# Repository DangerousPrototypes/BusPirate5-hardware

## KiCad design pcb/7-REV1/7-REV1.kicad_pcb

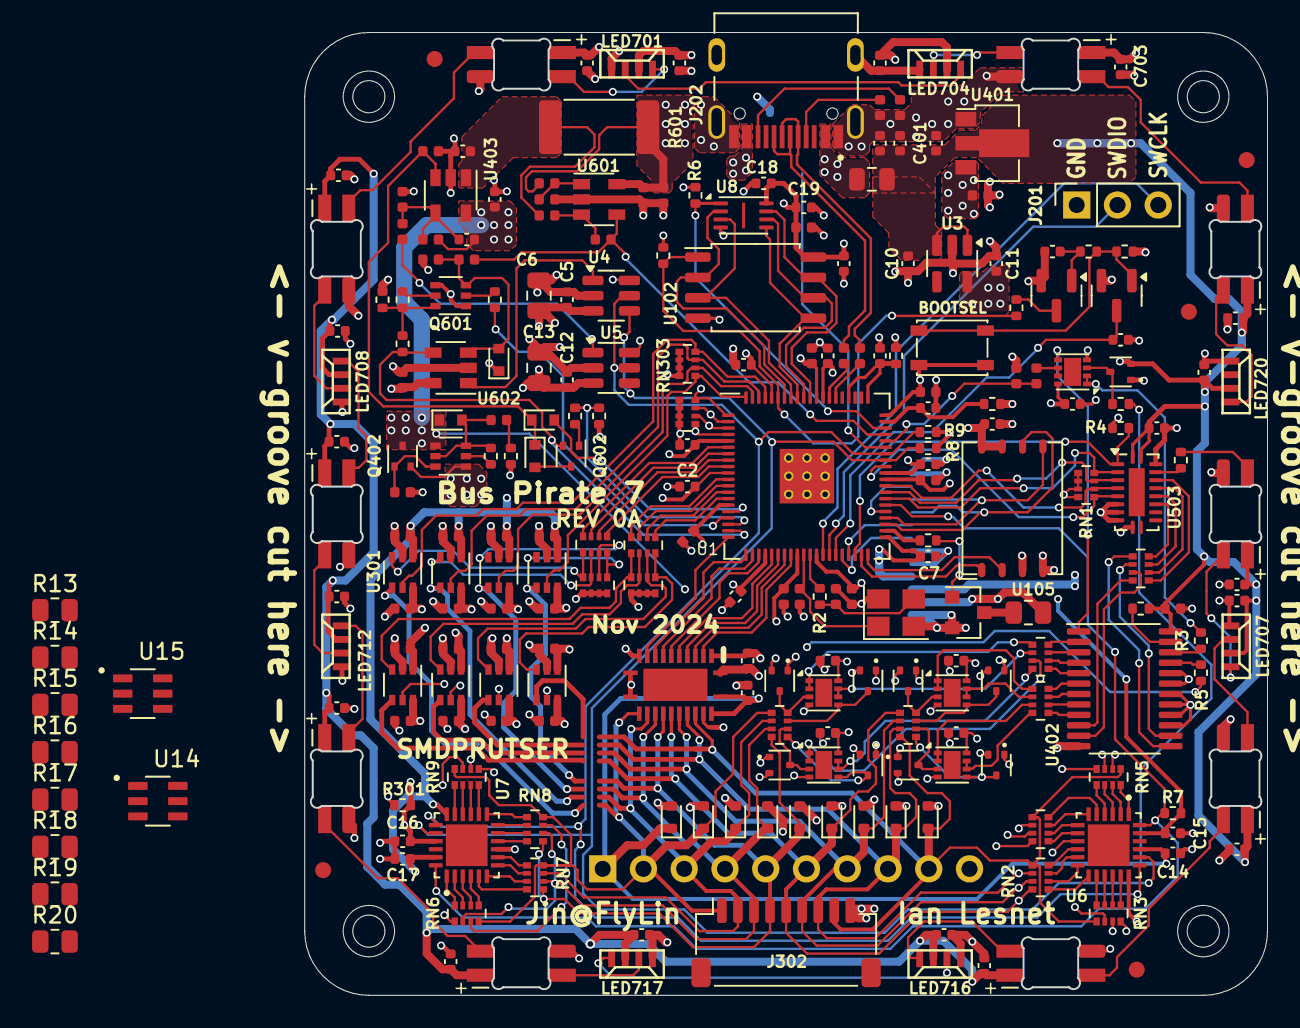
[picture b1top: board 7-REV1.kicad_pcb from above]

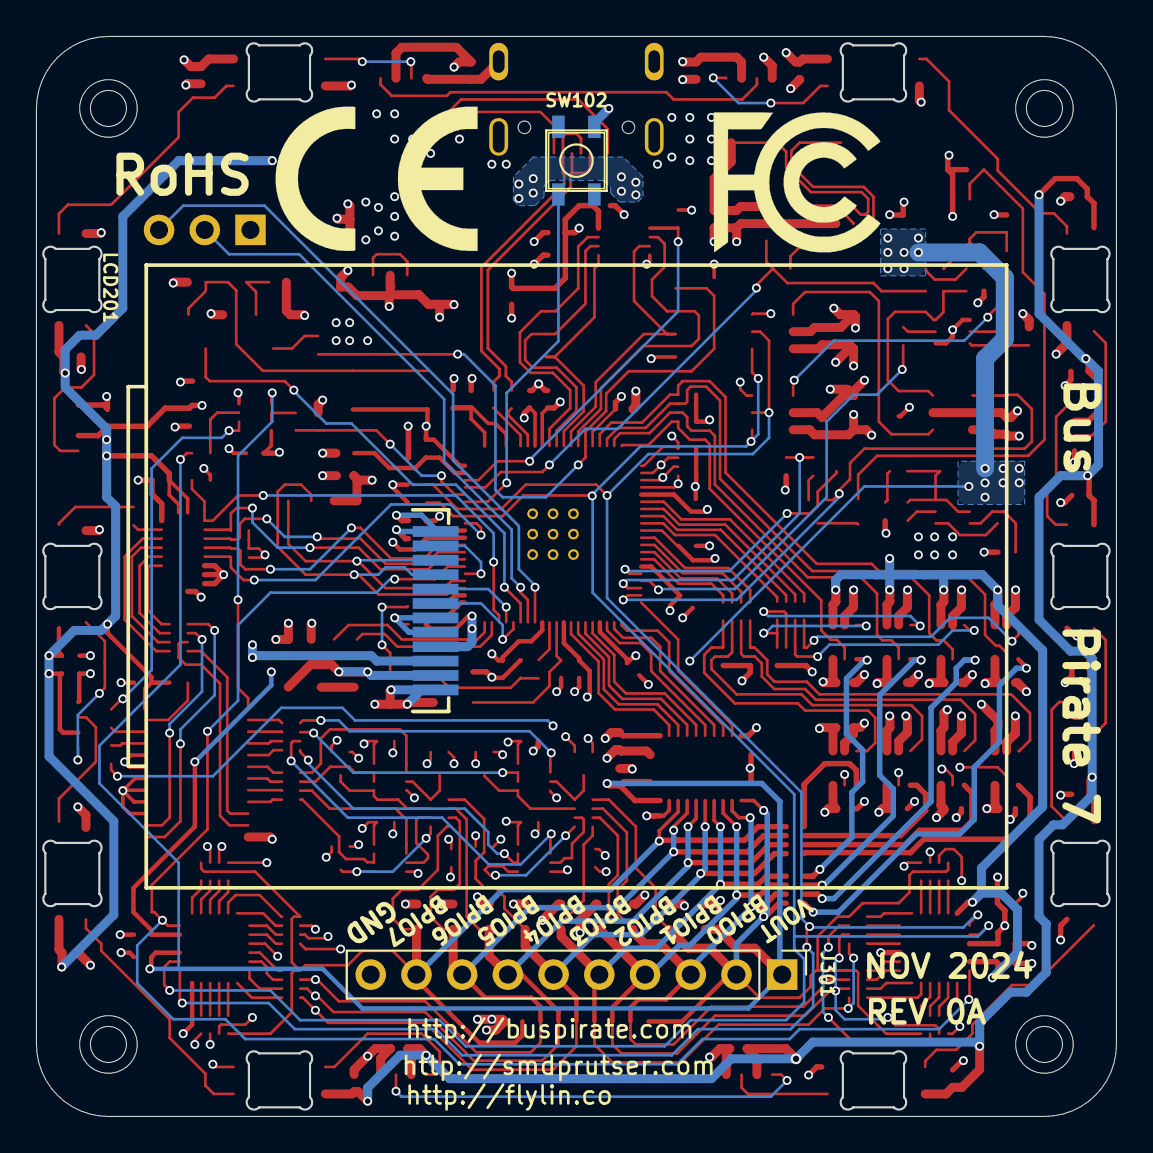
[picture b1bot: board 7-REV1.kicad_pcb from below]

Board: 4 copper layers, 60.0 x 60.0 mm, 260 parts (5 on the bottom side), 212 nets.

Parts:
C1, C2, C3, C5, C7, C8, C9, C12, C14, C15, C16, C17, C18, C20, C22, C103, C110, C111, C112, C113, C114, C115, C116, C117, C118, C121, C301, C302, C303, C304, C305, C306, C307, C308, C309, C310, C311, C312, C313, C314, C315, C316, C403, C503, C507, C508, C509, C510, C602, C605, C701, C702, C703, C704, C705, C706, C707, C708, C710, C712, C713, C714, C715, C716, C717, C718, C719, C720: 0.1uF; C_0402_1005Metric
C4, C19, C104, C109, C601: 2.2uF; C_0402_1005Metric
C6, C13: 10uF; C_0805_2012Metric
C10, C11, C201, C202, C401, C402, C404, C407: 4.7uF; C_0402_1005Metric
C21: 10uF; C_0402_1005Metric
C105, C106: 15pF; C_0402_1005Metric
C408: 120pF; C_0402_1005Metric
C603: DNF; C_0402_1005Metric
D1, D2, D3, D4, D5, D6, D7, D8, D9: BAS40-04; SOT-523
D10, D11, D12, D13, D14, D15, D16, D17, D18: DESD5Z5.0; D_SOD-523
D401, D601, D602, D603: 1N4148WT; D_SOD-523
FID1, FID2, FID3, FID4, FID5: Fiducial; Fiducial_1mm_Mask2mm
H1, H2, H3, H4: MountingHole; MountingHole_3.2mm_M3
J201: Conn_01x03; PinSocket_1x03_P2.54mm_Vertical
J202: TYPE-C-31-M-12; HRO_TYPE-C-31-M-12
J301: Conn_01x10; PinHeader_1x10_P2.54mm_Vertical
J302: Conn_01x09; JST_SH_SM09B-SRSS-TB_1x09-1MP_P1.00mm_Horizontal
L201: CBW201209U300T; L_0805_2012Metric
LCD201: TFT_20_QT200H1201
LED701, LED704, LED707, LED708, LED712, LED716, LED717, LED720: SK6812-side-a_b
LED702, LED703, LED705, LED706, LED710, LED713, LED714, LED715, LED718, LED719: SK6812-mini-e; SK6812-MINI-E
Q1, Q2, Q202: MMBT7002K; SOT-23
Q401: BCM857; SOT-363_SC-70-6
Q402, Q602: BC2301T 2.8A; SOT-523
Q601: MMDT3906; SOT-363_SC-70-6
R1: 10R; R_0402_1005Metric
R2, R12, R502, R602, R603: 1K; R_0402_1005Metric
R3, R5, R320: 510R; R_0402_1005Metric
R4, R6, R7, R319, R401, R412: 100K; R_0402_1005Metric
R8, R9, R11, R301, R406, R407, R410, R606, R609, R610, R611, R613: 10K; R_0402_1005Metric
R10: 470K; R_0402_1005Metric
R13, R14, R15, R16, R17, R18, R19, R20: 120R; R_0805_2012Metric
R102: DNF; R_0402_1005Metric
R103, R208, R608, R612: 200R; R_0402_1005Metric
R201, R204: 5.1K; R_0402_1005Metric
R202, R203: 22R; R_0402_1005Metric
R209: 33R; R_0805_2012Metric
R403: 102K; R_0402_1005Metric
R404: 133K; R_0402_1005Metric
R405, R408, R409, R604, R605: 33K; R_0402_1005Metric
R601: 0R2; R_2512_6332Metric_Pad1.40x3.35mm_HandSolder
RN1, RN302, RN303, RN307, RN308, RN317, RN318: 100K; R_Array_Convex_4x0402
RN2, RN8: 1M; R_Array_Convex_4x0402
RN3, RN9: 10K; R_Array_Convex_4x0402
RN4, RN7: 4.7K; R_Array_Convex_4x0402
RN5, RN6: 2.2K; R_Array_Convex_4x0402
RN301, RN306: 330R; R_Array_Convex_4x0402
RN315, RN400, RN401: 510R; R_Array_Convex_4x0402
SW101: TS3425BA 098 2.5H 250gf; SW_SPST_PTS810
SW102: TS3315A 250gf 025; GT-TC026X-HXXX-LX
U1: RP2350B; qfn80
U2: 74LVC8T245BQ; NXP-DHVQFN24
U3: TLV74311PDBVR; SOT-23-5
U4, U5: MCP4725xxx-xCH; SOT-23-6
U6, U7: TCA6416RTWT; QFN50P400X400X80-25N
U8: APS6404L-3SQR-ZR; Winbond_USON-8-1EP_3x2mm_P0.5mm_EP0.2x1.6mm
U9, U10, U11, U12, U13: LM358_DFN; DFN-8-1EP_2x2mm_P0.5mm_EP1.05x1.75mm
U14, U15: IP4220CZ6F; SOT95P275X110-6N
U102: W25Q128JVSIQ; SOP-8_5.28x5.23mm_P1.27mm
U105: MT29F1G01ABAFDWB; U-PDFN-8
U301, U302, U303, U304, U305, U306, U307, U308: AiP74LVC1T45GC363.TR; SOT-363_SC-70-6
U401: ME6211A33PG-N; SOT-89-3
U402: CD4067; TSSOP-24_4.4x7.8mm_P0.65mm
U403: AP2127; SOT-23-5
U503: 74HCT245BQ; DHVQFN-20-1EP_2.5x4.5mm_P0.5mm_EP1x3mm
U601: GS321A-TR; SOT-23-5
U602: GSV331-TR; SOT-23-5
Y101: ABM8-272-T3; Crystal_SMD_3225-4Pin_3.2x2.5mm
logo1: fcc_logo; logo_fcc
logo2: ce_logo; CE-Logo_11.2x8mm_SilkScreen

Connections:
+1V1: C2.1, C11.1, C117.1, C118.1, U1.10 (DVDD), U1.32 (DVDD), U1.51 (DVDD), U3.5 (VOUT)
+3V3: C1.1, C3.2, C5.1, C6.1, C7.1, C8.1, C12.1, C13.1, C15.2, C17.2, C18.1, C19.1, C103.1, C104.1, C110.1, C111.1, C112.1, C113.1, C114.1, C115.1, C116.1, C121.1, C301.2, C302.2, C303.2, C307.2, C308.2, C309.2, C313.2, C314.2, C402.1, C605.1, D601.1 (K), LCD201.4 (VCC), Q601.1 (E1), Q601.4 (E2), R1.1, R6.1, R7.1, R8.1, R9.1, R102.1, R103.1, R609.1, R613.1, SW101.1 (A), U1.5 (IOVDD), U1.15 (IOVDD), U1.24 (IOVDD), U1.29 (IOVDD), U1.41 (IOVDD), U1.50 (IOVDD), U1.60 (IOVDD), U1.68 (USB_OTP_VDD), U1.69 (QSPI_IOVDD), U1.76 (IOVDD), U2.1 (VCCA), U4.3 (VDD), U5.3 (VDD), U5.6 (A0), U6.23 (VCCI), U7.18 (ADDR), U7.23 (VCCI), U8.8 (VCC), U102.8 (VCC), U105.3 (WP/IO2), U105.7 (HOLD/IO3), U105.8 (VCC), U301.1 (VCCA), U302.1 (VCCA), U303.1 (VCCA), U304.1 (VCCA), U305.1 (VCCA), U306.1 (VCCA), U307.1 (VCCA), U308.1 (VCCA), U401.3 (VOUT), U602.5 (V+)
+VUSB: C10.1, C20.2, C201.2, C202.2, C401.1, C403.2, C503.2, C507.2, C508.2, C509.2, C510.2, C601.1, C602.2, C701.2, C702.2, C703.2, C704.2, C705.2, C706.2, C707.2, C708.2, C710.2, C712.2, C713.2, C714.2, C715.2, C716.2, C717.2, C718.2, C719.2, C720.2, D1.2, D2.2, D3.2, D4.2, D5.2, D6.2, D7.2, D8.2, D9.2, L201.1, LCD201.3 (LED-A), LED701.3 (VDD), LED702.1 (VDD), LED703.1 (VDD), LED704.3 (VDD), LED705.1 (VDD), LED706.1 (VDD), LED707.3 (VDD), LED708.3 (VDD), LED710.1 (VDD), LED712.3 (VDD), LED713.1 (VDD), LED714.1 (VDD), LED715.1 (VDD), LED716.3 (VDD), LED717.3 (VDD), LED718.1 (VDD), LED719.1 (VDD), LED720.3 (VDD), R320.2, R601.1, R602.2, U3.1 (VIN), U3.3 (~SHDN), U9.8 (V+), U10.8 (V+), U11.8 (V+), U12.8 (V+), U13.8 (V+), U14.5 (VP), U15.5 (VP), U401.2 (VIN), U402.24 (VCC), U503.1 (A->B), U503.20 (VCC), U601.5 (V+)
AMUX_OUT: R406.2, R407.2, U1.56 (GPIO45_ADC5)
AMUX_S0: RN315.4 (R1.1), U402.10 (S0)
AMUX_S0_3V3: RN1.8 (R1.8), U1.47 (GPIO38), U503.3 (A1)
AMUX_S1: RN315.3 (R1.1), U402.11 (S1)
AMUX_S1_3V3: RN1.7 (R1.8), U1.48 (GPIO39), U503.4 (A2)
AMUX_S2: RN315.2 (R1.1), U402.14 (S2)
AMUX_S2_3V3: RN1.6 (R1.8), U1.49 (GPIO40_ADC0), U503.5 (A3)
AMUX_S3: RN315.1 (R1.1), U402.13 (S3)
AMUX_S3_3V3: RN1.5 (R1.8), U1.52 (GPIO41_ADC1), U503.6 (A4)
BPIO0: D10.1 (K), R13.1, RN6.4 (R1.1), RN7.4 (R1.1), RN8.8 (R1.8), RN9.8 (R1.8), RN318.5 (R1.8), U2.14 (B8), U14.1 (I/O_1), U301.4 (B)
BPIO1: D11.1 (K), R14.1, RN6.3 (R1.1), RN7.3 (R1.1), RN8.7 (R1.8), RN9.7 (R1.8), RN318.6 (R1.8), U2.15 (B7), U14.3 (I/O_2), U302.4 (B)
BPIO2: D13.1 (K), R15.1, RN6.2 (R1.1), RN7.2 (R1.1), RN8.6 (R1.8), RN9.6 (R1.8), RN318.7 (R1.8), U2.16 (B6), U14.4 (I/O_3), U303.4 (B)
BPIO3: D12.1 (K), R16.1, RN6.1 (R1.1), RN7.1 (R1.1), RN8.5 (R1.8), RN9.5 (R1.8), RN318.8 (R1.8), U2.17 (B5), U14.6 (I/O_4), U304.4 (B)
BPIO4: D17.1 (K), R17.1, RN2.8 (R1.8), RN3.8 (R1.8), RN4.4 (R1.1), RN5.4 (R1.1), RN317.5 (R1.8), U2.18 (B4), U15.1 (I/O_1), U305.4 (B)
BPIO5: D16.1 (K), R18.1, RN2.7 (R1.8), RN3.7 (R1.8), RN4.3 (R1.1), RN5.3 (R1.1), RN317.6 (R1.8), U2.19 (B3), U15.3 (I/O_2), U306.4 (B)
BPIO6: D15.1 (K), R19.1, RN2.6 (R1.8), RN3.6 (R1.8), RN4.2 (R1.1), RN5.2 (R1.1), RN317.7 (R1.8), U2.20 (B2), U15.4 (I/O_3), U307.4 (B)
BPIO7: D14.1 (K), R20.1, RN2.5 (R1.8), RN3.5 (R1.8), RN4.1 (R1.1), RN5.1 (R1.1), RN317.8 (R1.8), U2.21 (B1), U15.6 (I/O_4), U308.4 (B)
BUFDIR0: RN303.8 (R1.8), U1.77 (GPIO0), U301.5 (DIR)
BUFDIR1: RN303.7 (R1.8), U1.78 (GPIO1), U302.5 (DIR)
BUFDIR2: RN303.6 (R1.8), U1.79 (GPIO2), U303.5 (DIR)
BUFDIR3: RN303.5 (R1.8), U1.80 (GPIO3), U304.5 (DIR)
BUFDIR4: RN308.8 (R1.8), U1.1 (GPIO4), U305.5 (DIR)
BUFDIR5: RN308.7 (R1.8), U1.2 (GPIO5), U306.5 (DIR)
BUFDIR6: RN308.6 (R1.8), U1.3 (GPIO6), U307.5 (DIR)
BUFDIR7: RN308.5 (R1.8), U1.4 (GPIO7), U308.5 (DIR)
BUFIO0: RN301.8 (R1.8), U1.6 (GPIO8)
BUFIO1: RN301.7 (R1.8), U1.7 (GPIO9)
BUFIO2: RN301.6 (R1.8), U1.8 (GPIO10)
BUFIO3: RN301.5 (R1.8), U1.9 (GPIO11)
BUFIO4: RN306.8 (R1.8), U1.11 (GPIO12)
BUFIO5: RN306.7 (R1.8), U1.12 (GPIO13)
BUFIO6: RN306.6 (R1.8), U1.13 (GPIO14)
BUFIO7: RN306.5 (R1.8), U1.14 (GPIO15)
BUTTONS: SW102.1, U1.55 (GPIO44_ADC4)
CURRENT_ADJ_MCU: U4.1 (VOUT), U602.1 (+)
CURRENT_DETECT: Q602.2 (S), R610.2, U1.19 (GPIO19), U602.4
CURRENT_EN: R612.2, R613.2, U1.18 (GPIO18)
CURRENT_EN_OVERRIDE: D603.2 (A), U1.16 (GPIO16)
CURRENT_RESET: R611.1, U1.17 (GPIO17)
CURRENT_SENSE: R605.1, R606.2, U1.57 (GPIO46_ADC6), U601.4
DISPLAY_BACKLIGHT: R208.1, U1.42 (GPIO33)
DISPLAY_CS: LCD201.8 (CS), U1.37 (GPIO29)
DISPLAY_DP: LCD201.7 (WR/SPI_A0), U1.36 (GPIO28)
DISPLAY_LED-K: LCD201.2 (LED-K), R209.2
DISPLAY_RESET: LCD201.11 (RESET), U1.45 (GPIO36)
FLASH_CS: U1.39 (GPIO31), U105.1 (CS)
GND: C1.2, C2.2, C3.1, C4.2, C5.2, C6.2, C7.2, C8.2, C9.2, C10.2, C11.2, C12.2, C13.2, C14.1, C15.1, C16.1, C17.1, C18.2, C19.2, C20.1, C21.2, C22.2, C103.2, C104.2, C105.2, C106.2, C109.2, C110.2, C111.2, C112.2, C113.2, C114.2, C115.2, C116.2, C117.2, C118.2, C121.2, C201.1, C202.1, C301.1, C302.1, C303.1, C304.2, C305.2, C306.2, C307.1, C308.1, C309.1, C310.2, C311.2, C312.2, C313.1, C314.1, C315.2, C316.2, C401.2, C402.2, C403.1, C404.2, C407.2, C503.1, C507.1, C508.1, C509.1, C510.1, C601.2, C602.1, C603.1, C605.2, C701.1, C702.1, C703.1, C704.1, C705.1, C706.1, C707.1, C708.1, C710.1, C712.1, C713.1, C714.1, C715.1, C716.1, C717.1, C718.1, C719.1, C720.1, D1.1, D2.1, D3.1, D4.1, D5.1, D6.1, D7.1, D8.1, D9.1, D10.2 (A), D11.2 (A), D12.2 (A), D13.2 (A), D14.2 (A), D15.2 (A), D16.2 (A), D17.2 (A), D18.2 (A), J201.1, J202.A1B12 (GND), J202.B1A12 (GND), J202.S1 (SHIELD), J202.S2 (SHIELD), J202.S3 (SHIELD), J202.S4 (SHIELD), J301.10, J302.9, LCD201.1 (GND), LCD201.5 (GND), LCD201.6 (GND), LCD201.12 (GND), LED701.1 (VSS), LED702.3 (VSS), LED703.3 (VSS), LED704.1 (VSS), LED705.3 (VSS), LED706.3 (VSS), LED707.1 (VSS), LED708.1 (VSS), LED710.3 (VSS), LED712.1 (VSS), LED713.3 (VSS), LED714.3 (VSS), LED715.3 (VSS), LED716.1 (VSS), LED717.1 (VSS), LED718.3 (VSS), LED719.3 (VSS), LED720.1 (VSS), Q1.2 (S), Q2.2 (S), Q202.2 (S), R4.1, R11.2, R201.1, R204.1, R301.2, R401.2, R405.2, R407.1, R409.2, R412.2, R604.1, RN1.1 (R1.1), RN1.2 (R1.1), RN1.3 (R1.1), RN1.4 (R1.1), RN302.1 (R1.1), RN302.2 (R1.1), RN302.3 (R1.1), RN302.4 (R1.1), RN303.1 (R1.1), RN303.2 (R1.1), RN303.3 (R1.1), RN303.4 (R1.1), RN307.1 (R1.1), RN307.2 (R1.1), RN307.3 (R1.1), RN307.4 (R1.1), RN308.1 (R1.1), RN308.2 (R1.1), RN308.3 (R1.1), RN308.4 (R1.1), SW102.4, U1.81 (GND), U2.2 (DIR), U2.11 (GND), U2.12 (GND), U2.13 (GND), U2.22 (~OE), U3.2 (GND), U4.2 (VSS), U4.6 (A0), U5.2 (VSS), U6.9 (GND), U6.18 (ADDR), U7.9 (GND), U8.4 (VSS), U9.4 (V-), U10.4 (V-), U11.4 (V-), U12.4 (V-), U13.4 (V-), U14.2 (GND), U15.2 (GND), U102.4 (VSS), U105.4 (VSS), U301.2 (GND), U302.2 (GND), U303.2 (GND), U304.2 (GND), U305.2 (GND), U306.2 (GND), U307.2 (GND), U308.2 (GND), U401.1 (GND), U402.12 (GND), U402.15 (~E), U402.16 (I15), U402.17 (I14), U402.18 (I13), U402.19 (I12), U402.20 (I11), U403.2 (GND), U503.7 (A5), U503.8 (A6), U503.9 (A7), U503.10 (GND), U503.19 (CE), U601.2 (V-), U602.2 (V-), Y101.2, Y101.4
I2C_RESET: R7.2, U1.46 (GPIO37), U6.24 (~RESET), U7.24 (~RESET)
I2C_SCL: R9.2, U1.54 (GPIO43_ADC3), U4.5 (SCL), U5.5 (SCL), U6.19 (SCL), U7.19 (SCL)
I2C_SDA: R8.2, U1.53 (GPIO42_ADC2), U4.4 (SDA), U5.4 (SDA), U6.20 (SDA), U7.20 (SDA)
LA_BPIO0: U1.20 (GPIO20), U2.10 (A8)
LA_BPIO1: U1.21 (GPIO21), U2.9 (A7)
LA_BPIO2: U1.22 (GPIO22), U2.8 (A6)
LA_BPIO3: U1.23 (GPIO23), U2.7 (A5)
LA_BPIO4: U1.25 (GPIO24), U2.6 (A4)
LA_BPIO5: U1.26 (GPIO25), U2.5 (A3)
LA_BPIO6: U1.27 (GPIO26), U2.4 (A2)
LA_BPIO7: U1.28 (GPIO27), U2.3 (A1)
LEDS_CDO: R502.1, U503.18 (B0)
MCU_BOOTLOAD: R12.2, R102.2, U1.75 (QSPI_SS), U102.1 (CS)
MCU_RESET: C22.1, Q1.3 (D), U1.35 (RUN)
MUX_BPIO0: RN401.5 (R1.8), U9.1, U9.2 (-)
MUX_BPIO1: RN401.6 (R1.8), U9.6 (-), U9.7
MUX_BPIO2: RN401.7 (R1.8), U10.1, U10.2 (-)
MUX_BPIO3: RN401.8 (R1.8), U10.6 (-), U10.7
MUX_BPIO4: RN400.5 (R1.8), U11.1, U11.2 (-)
MUX_BPIO5: RN400.6 (R1.8), U11.6 (-), U11.7
MUX_BPIO6: RN400.7 (R1.8), U12.1, U12.2 (-)
MUX_BPIO7: RN400.8 (R1.8), U12.6 (-), U12.7
MUX_VREF_VOUT: R3.2, U13.1, U13.2 (-)
unnamed: C106.1, R2.1, Y101.3
unnamed: D401.2 (A), Q401.3 (C2), Q401.5 (B2), R408.2, R410.2
unnamed: C603.2, D601.2 (A), Q601.3 (C2), R606.1, U602.3 (-)
unnamed: D602.2 (A), Q602.3 (D)
unnamed: J202.A5 (CC1), R201.2
unnamed: J202.B5 (CC2), R204.2
unnamed: J202.A4B9 (VBUS), J202.B4A9 (VBUS), L201.2
unnamed: J301.2, J302.1, R13.2
unnamed: J301.3, J302.2, R14.2
unnamed: J301.4, J302.3, R15.2
unnamed: J301.5, J302.4, R16.2
unnamed: J301.6, J302.5, R17.2
unnamed: J301.7, J302.6, R18.2
unnamed: J301.8, J302.7, R19.2
unnamed: J301.9, J302.8, R20.2
unnamed: LED701.4 (DI), LED702.2 (DO)
unnamed: LED701.2 (DO), LED704.4 (DI)
unnamed: LED702.4 (DI), LED706.2 (DO)
unnamed: LED703.4 (DI), LED704.2 (DO)
unnamed: LED703.2 (DO), LED705.4 (DI)
unnamed: LED705.2 (DO), LED720.4 (DI)
unnamed: LED706.4 (DI), LED708.2 (DO)
unnamed: LED707.4 (DI), LED719.2 (DO)
unnamed: LED707.2 (DO), LED713.4 (DI)
unnamed: LED708.4 (DI), LED710.2 (DO)
unnamed: LED710.4 (DI), LED712.2 (DO)
unnamed: LED712.4 (DI), LED714.2 (DO)
unnamed: LED713.2 (DO), LED715.4 (DI)
unnamed: LED714.4 (DI), LED718.2 (DO)
unnamed: LED715.2 (DO), LED716.4 (DI)
unnamed: LED716.2 (DO), LED717.4 (DI)
unnamed: LED717.2 (DO), LED718.4 (DI)
unnamed: LED719.4 (DI), R502.2
unnamed: Q1.1 (G), R10.1, R11.1, SW101.2 (B)
unnamed: Q2.3 (D), R12.1
unnamed: C21.1, Q2.1 (G), R10.2
unnamed: Q202.3 (D), R209.1
unnamed: Q202.1 (G), R208.2
unnamed: Q401.2 (B1), R410.1
unnamed: Q401.6 (C1), Q402.1 (G), R412.1
unnamed: Q601.2 (B1), R611.2
unnamed: Q601.6 (C1), R608.2, R609.2, R610.1
unnamed: Q601.5 (B2), R608.1
unnamed: Q602.1 (G), R612.1
unnamed: R408.1, R409.1
unnamed: RN2.1 (R1.1), U6.13
unnamed: RN2.2 (R1.1), U6.12
unnamed: RN2.3 (R1.1), U6.11
unnamed: RN2.4 (R1.1), U6.10
unnamed: RN3.1 (R1.1), U6.17
unnamed: RN3.2 (R1.1), U6.16
unnamed: RN3.3 (R1.1), U6.15
unnamed: RN3.4 (R1.1), U6.14
unnamed: RN4.8 (R1.8), U6.5 (P04)
unnamed: RN4.7 (R1.8), U6.6 (P05)
unnamed: RN4.6 (R1.8), U6.7 (P06)
unnamed: RN4.5 (R1.8), U6.8 (P07)
unnamed: RN5.8 (R1.8), U6.1 (P00)
unnamed: RN5.7 (R1.8), U6.2 (P01)
unnamed: RN5.6 (R1.8), U6.3 (P02)
unnamed: RN5.5 (R1.8), U6.4 (P03)
unnamed: RN6.8 (R1.8), U7.1 (P00)
unnamed: RN6.7 (R1.8), U7.2 (P01)
unnamed: RN6.6 (R1.8), U7.3 (P02)
unnamed: RN6.5 (R1.8), U7.4 (P03)
unnamed: RN7.8 (R1.8), U7.5 (P04)
unnamed: RN7.7 (R1.8), U7.6 (P05)
unnamed: RN7.6 (R1.8), U7.7 (P06)
unnamed: RN7.5 (R1.8), U7.8 (P07)
unnamed: RN8.1 (R1.1), U7.13
unnamed: RN8.2 (R1.1), U7.12
unnamed: RN8.3 (R1.1), U7.11
unnamed: RN8.4 (R1.1), U7.10
unnamed: RN9.1 (R1.1), U7.17
unnamed: RN9.2 (R1.1), U7.16
unnamed: RN9.3 (R1.1), U7.15
unnamed: RN9.4 (R1.1), U7.14
unnamed: RN301.1 (R1.1), RN302.8 (R1.8), U301.3 (A)
unnamed: RN301.2 (R1.1), RN302.7 (R1.8), U302.3 (A)
unnamed: RN301.3 (R1.1), RN302.6 (R1.8), U303.3 (A)
unnamed: RN301.4 (R1.1), RN302.5 (R1.8), U304.3 (A)
unnamed: RN306.1 (R1.1), RN307.8 (R1.8), U305.3 (A)
unnamed: RN306.2 (R1.1), RN307.7 (R1.8), U306.3 (A)
unnamed: RN306.3 (R1.1), RN307.6 (R1.8), U307.3 (A)
unnamed: RN306.4 (R1.1), RN307.5 (R1.8), U308.3 (A)
unnamed: RN315.8 (R1.8), U503.14 (B4)
unnamed: RN315.7 (R1.8), U503.15 (B3)
unnamed: RN315.6 (R1.8), U503.16 (B2)
unnamed: RN315.5 (R1.8), U503.17 (B1)
unnamed: D1.3, RN317.1 (R1.1), U12.5 (+)
unnamed: D2.3, RN317.2 (R1.1), U12.3 (+)
unnamed: D4.3, RN317.3 (R1.1), U11.5 (+)
unnamed: D3.3, RN317.4 (R1.1), U11.3 (+)
unnamed: D5.3, RN318.1 (R1.1), U10.5 (+)
unnamed: D6.3, RN318.2 (R1.1), U10.3 (+)
unnamed: D8.3, RN318.3 (R1.1), U9.5 (+)
unnamed: D7.3, RN318.4 (R1.1), U9.3 (+)
unnamed: RN400.1 (R1.1), U402.9 (I0)
unnamed: RN400.2 (R1.1), U402.8 (I1)
unnamed: RN400.3 (R1.1), U402.7 (I2)
unnamed: RN400.4 (R1.1), U402.6 (I3)
unnamed: RN401.1 (R1.1), U402.5 (I4)
unnamed: RN401.2 (R1.1), U402.4 (I5)
unnamed: RN401.3 (R1.1), U402.3 (I6)
unnamed: RN401.4 (R1.1), U402.2 (I7)
unnamed: C109.1, R103.2, U1.59 (ADC_AVDD)
unnamed: C4.1, R1.2, U1.61 (VREG_AVDD), U1.64 (VREG_VIN)
unnamed: C105.1, U1.30 (XIN), Y101.1
unnamed: R2.2, U1.31 (XOUT)
unnamed: D9.3, R319.1, U13.3 (+)
unnamed: U13.5 (+), U402.1 (COM)
unnamed: R406.1, U13.6 (-), U13.7
unnamed: R320.1, U402.23 (I8)
unnamed: R3.1, U402.22 (I9)
unnamed: R5.1, U402.21 (I10)
unnamed: C408.2, R403.2, R404.2, R405.1, U403.4 (ADJ)
unnamed: R602.1, R604.2, U601.1 (+)
unnamed: R603.1, R605.2, U601.3 (-)
QSPI_SCLK: U1.71 (QSPI_SCLK), U8.6 (CLK), U102.6 (CLK)
QSPI_SD0: U1.72 (QSPI_SD0), U8.5 (DI), U102.5 (DI)
QSPI_SD1: U1.74 (QSPI_SD1), U8.2 (DO), U102.2 (DO)
QSPI_SD2: U1.73 (QSPI_SD2), U8.3 (WP), U102.3 (WP)
QSPI_SD3: U1.70 (QSPI_SD3), U8.7 (HOLD), U102.7 (HOLD)
QSPI_SS_2: R6.2, U1.58 (GPIO47_ADC7), U8.1 (CS)
RGB_CDO: R4.2, U1.38 (GPIO30), U503.2 (A0)
SPI_CDI: U1.40 (GPIO32), U105.2 (SO/IO1)
SPI_CDO: LCD201.10 (SPI_SDA), U1.44 (GPIO35), U105.5 (SI/IO0)
SPI_CLK: LCD201.9 (RS/SPI_SCL), U1.43 (GPIO34), U105.6 (SCK)
SWCLK: J201.3, U1.33 (SWCLK)
SWDIO: J201.2, U1.34 (SWD)
USB_D+: R203.1, U1.67 (USB_DP)
USB_D-: R202.1, U1.66 (USB_DM)
USB_N: J202.A7 (DN1), J202.B7 (DN2), R202.2
USB_P: J202.A6 (DP1), J202.B6 (DP2), R203.2
VREF_VOUT: C9.1, C14.2, C16.2, C304.1, C305.1, C306.1, C310.1, C311.1, C312.1, C315.1, C316.1, D18.1 (K), J301.1, Q401.1 (E1), Q402.2 (S), R301.1, R319.2, U2.23 (VCCB), U2.24 (VCCB), U6.21 (VCCP), U7.21 (VCCP), U301.6 (VCCB), U302.6 (VCCB), U303.6 (VCCB), U304.6 (VCCB), U305.6 (VCCB), U306.6 (VCCB), U307.6 (VCCB), U308.6 (VCCB)
VREG_ADJ: R403.1, U5.1 (VOUT)
VREG_EN: D602.1 (K), D603.1 (K), R401.1, U403.3 (SHUTDOWN)
VREG_OUT: C407.1, C408.1, D401.1 (K), Q401.4 (E2), Q402.3 (D), R5.2, R404.1, U403.5 (OUT)
VREG_VIN: C404.1, R601.2, R603.2, U403.1 (VIN)

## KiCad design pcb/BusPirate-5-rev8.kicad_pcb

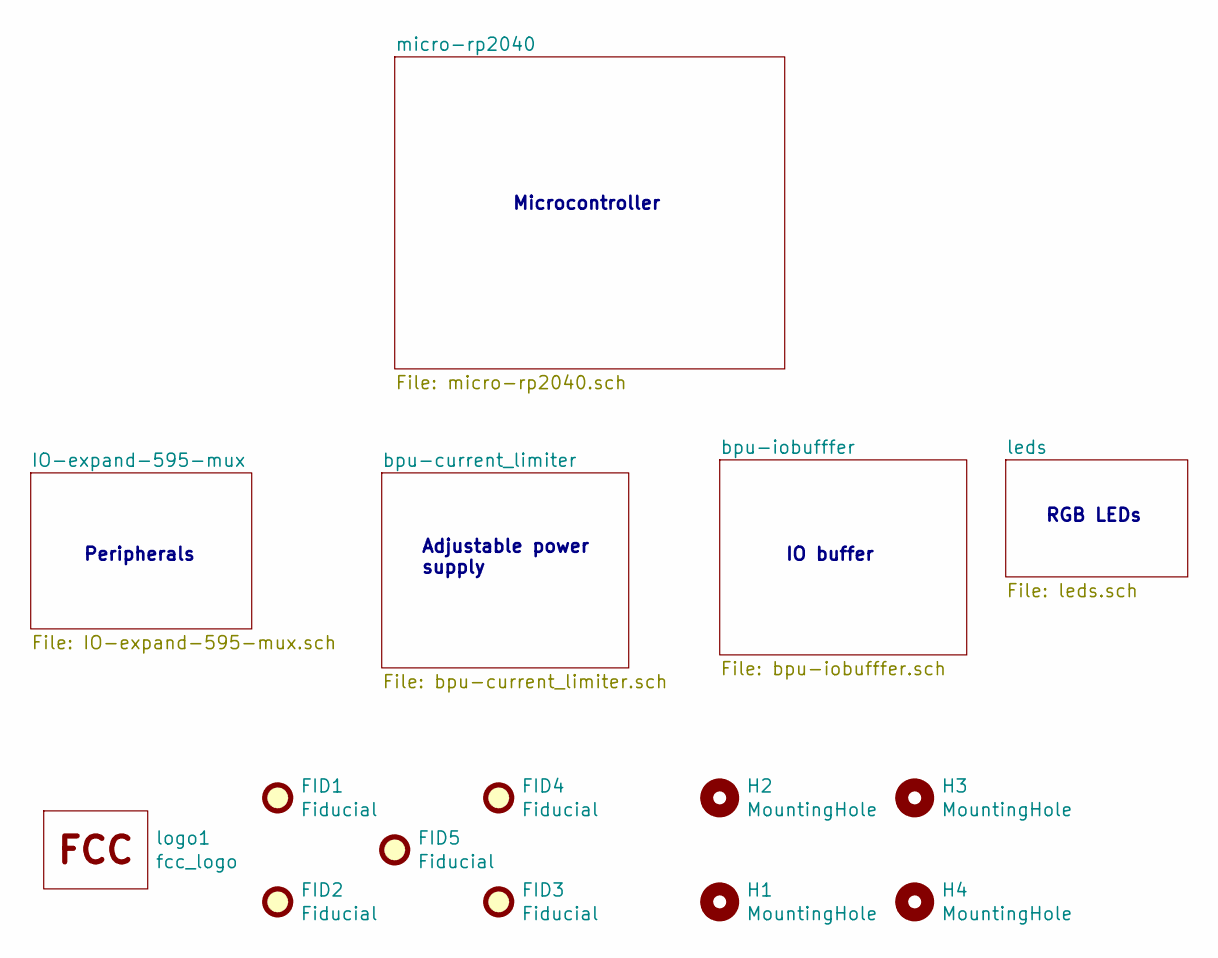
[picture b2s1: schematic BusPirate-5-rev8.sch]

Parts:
FID1, FID2, FID3, FID4, FID5: Fiducial; Fiducial_1mm_Mask2mm
H1, H2, H3, H4: MountingHole; MountingHole_3.2mm_M3
logo1: fcc_logo; logo_fcc

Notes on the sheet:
Microcontroller
Peripherals
Adjustable power supply
IO buffer
RGB LEDs

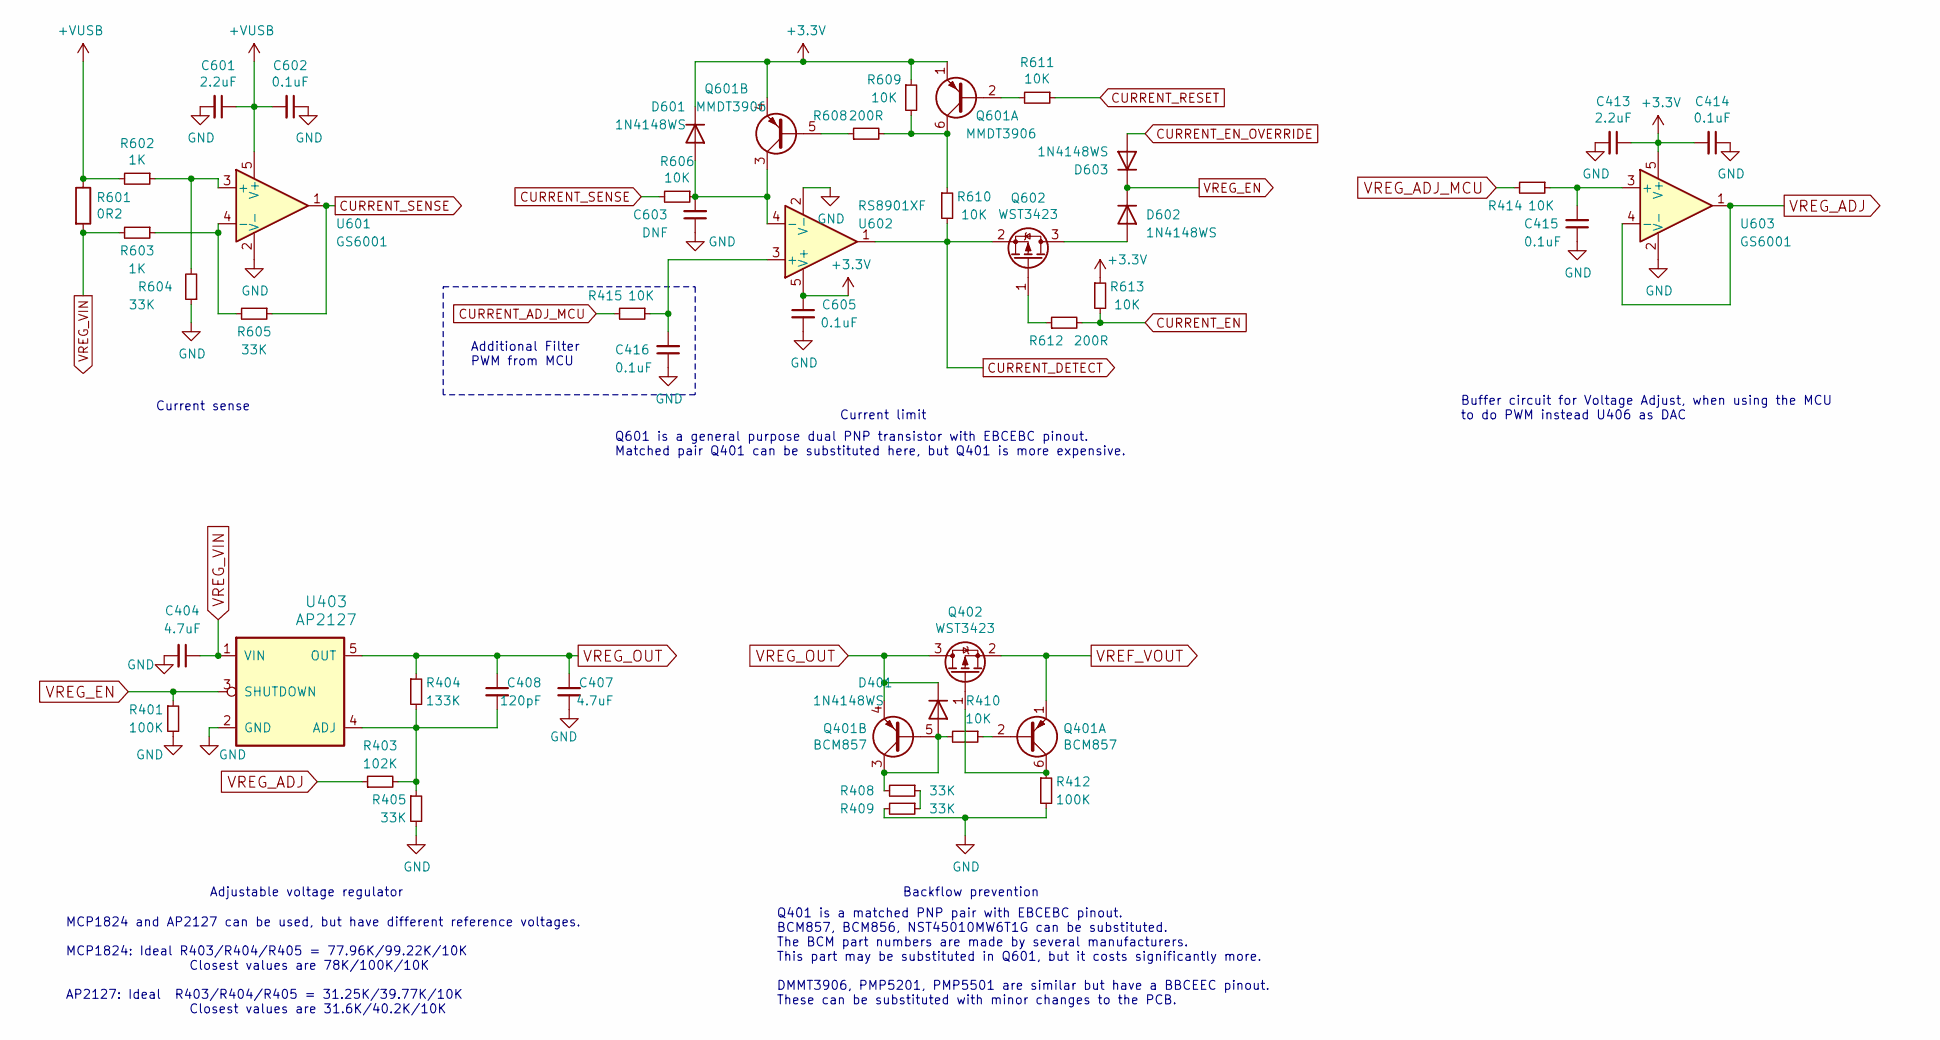
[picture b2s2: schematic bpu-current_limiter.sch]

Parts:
C404, C407: 4.7uF; C_0402_1005Metric
C408: 120pF; C_0402_1005Metric
C413, C601: 2.2uF; C_0402_1005Metric
C414, C415, C416, C602, C605: 0.1uF; C_0402_1005Metric
C603: DNF; C_0402_1005Metric
D401, D601, D602, D603: 1N4148WS; D_SOD-323
Q401: BCM857; SOT-363_SC-70-6
Q402, Q602: WST3423; SOT-23
Q601: MMDT3906; SOT-363_SC-70-6
R401, R412: 100K; R_0402_1005Metric
R403: 102K; R_0402_1005Metric
R404: 133K; R_0402_1005Metric
R405, R408, R409, R604, R605: 33K; R_0402_1005Metric
R410, R414, R415, R606, R609, R610, R611, R613: 10K; R_0402_1005Metric
R601: 0R2; R_2512_6332Metric_Pad1.40x3.35mm_HandSolder
R602, R603: 1K; R_0402_1005Metric
R608, R612: 200R; R_0402_1005Metric
U403: AP2127; SOT-23-5
U601, U603: GS6001; SOT-23-5
U602: RS8901XF; SOT-23-5

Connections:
+VUSB: C601.1, C602.2, R601.1, R602.2, U601.5 (V+); also elsewhere on the board
CURRENT_ADJ_MCU: R415.2; also elsewhere on the board
CURRENT_DETECT: Q602.2 (S), R610.2, U602.1; also elsewhere on the board
CURRENT_EN: R612.2, R613.2; also elsewhere on the board
CURRENT_EN_OVERRIDE: D603.2 (A); also elsewhere on the board
CURRENT_RESET: R611.1; also elsewhere on the board
CURRENT_SENSE: R605.1, R606.2, U601.1; also elsewhere on the board
GND: C404.2, C407.2, C413.2, C414.1, C415.1, C416.1, C601.2, C602.1, C603.1, C605.2, R401.2, R405.2, R409.2, R412.2, R604.1, U403.2 (GND), U601.2 (V-), U602.2 (V-), U603.2 (V-); also elsewhere on the board
unnamed: C408.2, R403.2, R404.2, R405.1, U403.4 (ADJ)
unnamed: C415.2, R414.1, U603.3 (+)
unnamed: C416.2, R415.1, U602.3 (+)
unnamed: C603.2, D601.2 (A), Q601.3 (C2), R606.1, U602.4 (-)
unnamed: D401.2 (A), Q401.3 (C2), Q401.5 (B2), R408.2, R410.2
unnamed: D602.2 (A), Q602.3 (D)
unnamed: Q401.2 (B1), R410.1
unnamed: Q401.6 (C1), Q402.1 (G), R412.1
unnamed: Q601.2 (B1), R611.2
unnamed: Q601.5 (B2), R608.1
unnamed: Q601.6 (C1), R608.2, R609.2, R610.1
unnamed: Q602.1 (G), R612.1
unnamed: R408.1, R409.1
unnamed: R602.1, R604.2, U601.3 (+)
unnamed: R603.1, R605.2, U601.4 (-)
VREF_VOUT: Q401.1 (E1), Q402.2 (S); also elsewhere on the board
VREG_ADJ: R403.1, U603.1, U603.4 (-)
VREG_ADJ_MCU: R414.2; also elsewhere on the board
VREG_EN: D602.1 (K), D603.1 (K), R401.1, U403.3 (SHUTDOWN)
VREG_OUT: C407.1, C408.1, D401.1 (K), Q401.4 (E2), Q402.3 (D), R404.1, U403.5 (OUT); also elsewhere on the board
VREG_VIN: C404.1, R601.2, R603.2, U403.1 (VIN)

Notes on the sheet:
Current sense
Current limit
Adjustable voltage regulator
Backflow prevention
MCP1824 and AP2127 can be used, but have different reference voltages. MCP1824: Ideal R403/R404/R405 = 77.96K/99.22K/10K Closest values are 78K/100K/10K AP2127: Ideal R403/R404/R405 = 31.25K/39.77K/10K Closest values are 31.6K/40.2K/10K
Q601 is a general purpose dual PNP transistor with EBCEBC pinout. Matched pair Q401 can be substituted here, but Q401 is more expensive.
Q401 is a matched PNP pair with EBCEBC pinout. BCM857, BCM856, NST45010MW6T1G can be substituted. The BCM part numbers are made by several manufacturers. This part may be substituted in Q601, but it costs significantly more. DMMT3906, PMP5201, PMP5501 are similar but have a BBCEEC pinout. These can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
Buffer circuit for Voltage Adjust, when using the MCU to do PWM instead U406 as DAC
Additional Filter PWM from MCU

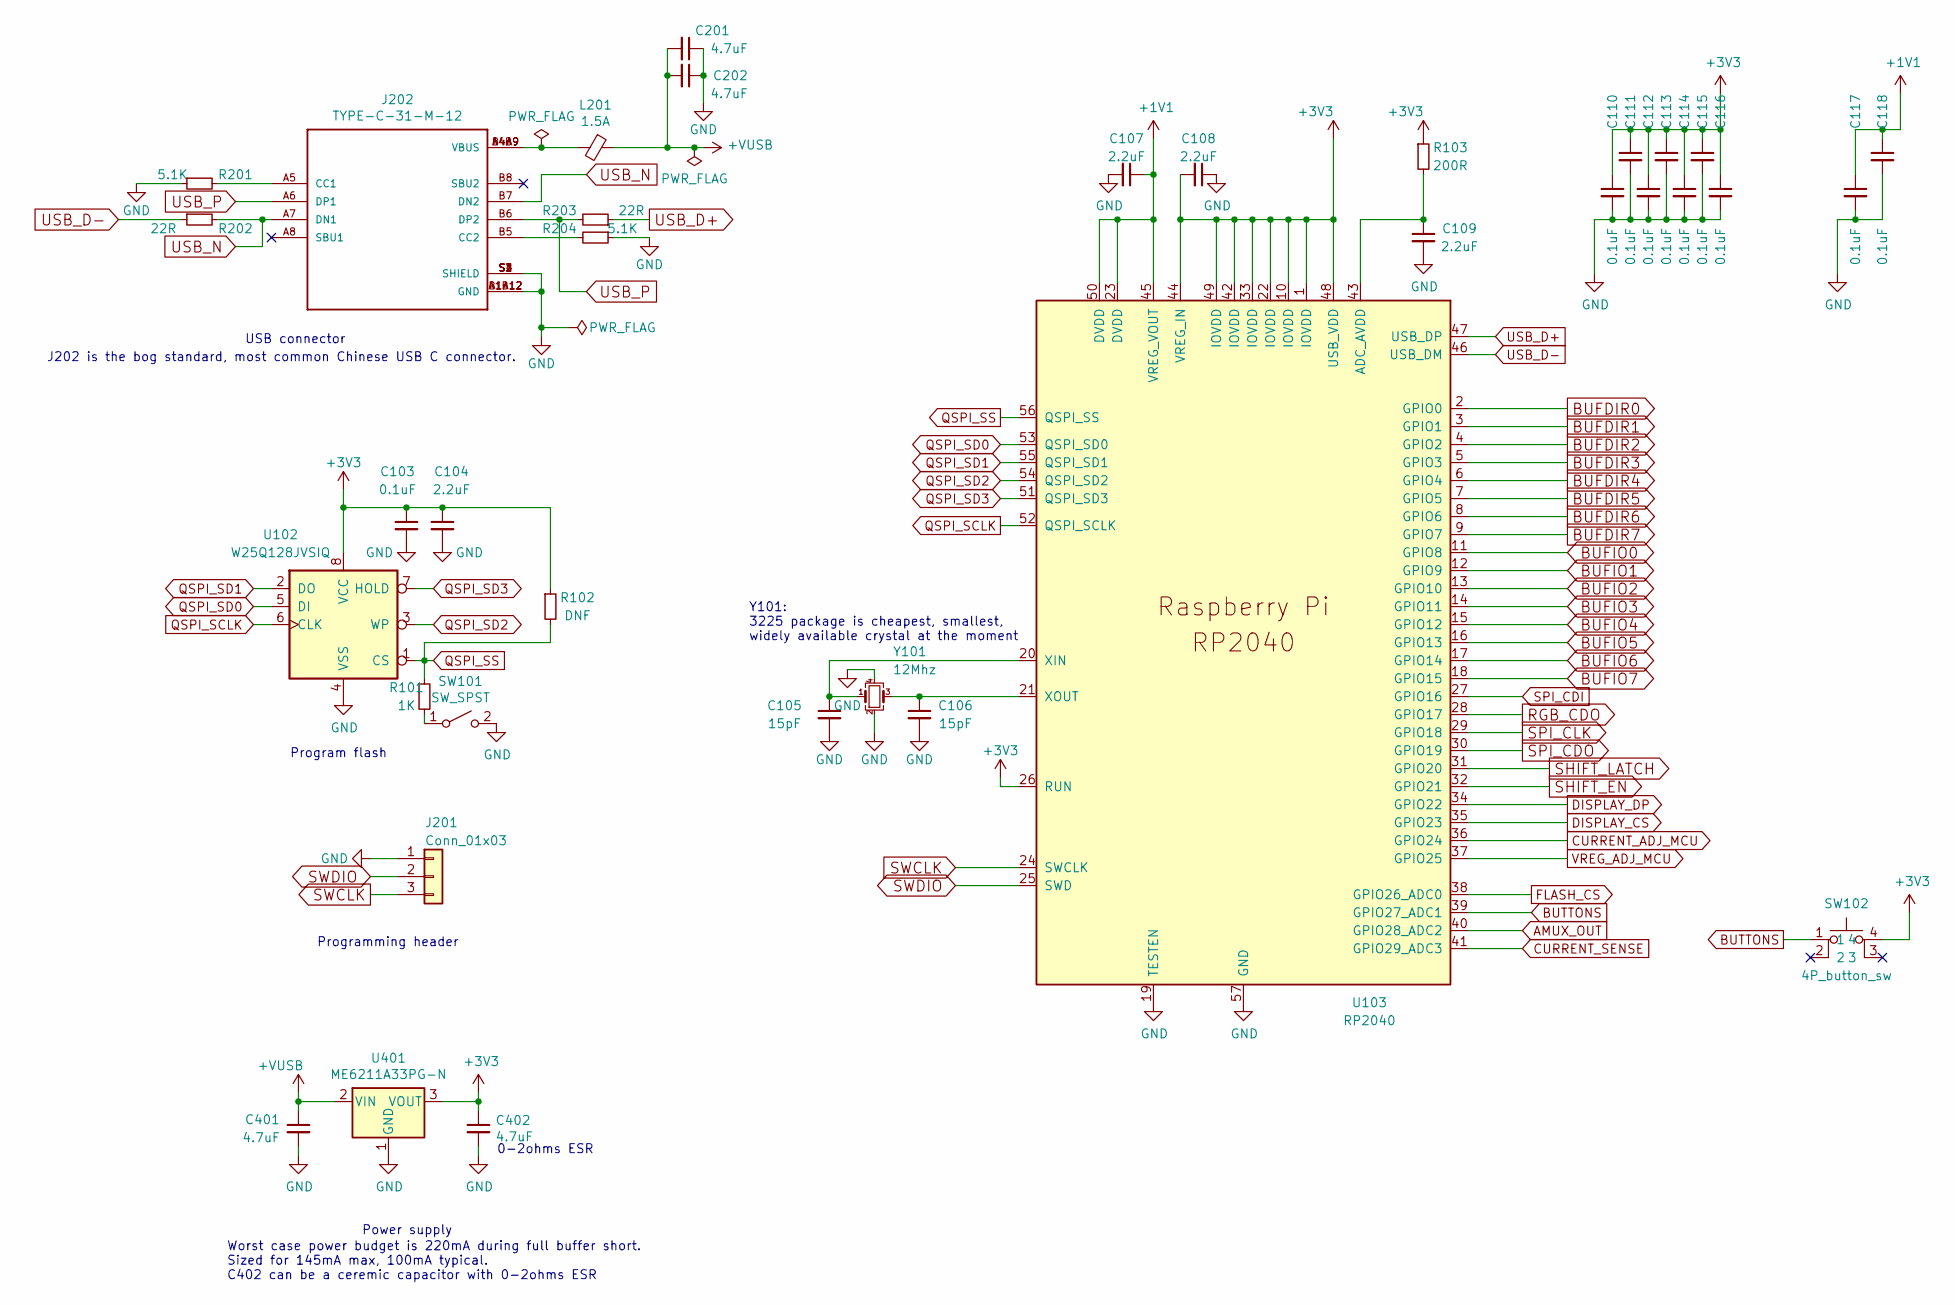
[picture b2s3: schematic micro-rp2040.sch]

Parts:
C103, C110, C111, C112, C113, C114, C115, C116, C117, C118: 0.1uF; C_0402_1005Metric
C104, C107, C108, C109: 2.2uF; C_0402_1005Metric
C105, C106: 15pF; C_0402_1005Metric
C201, C202, C401, C402: 4.7uF; C_0402_1005Metric
J201: Conn_01x03; PinSocket_1x03_P2.54mm_Vertical
J202: TYPE-C-31-M-12; HRO_TYPE-C-31-M-12
L201: 1.5A; L_0805_2012Metric
R101: 1K; R_0402_1005Metric
R102: DNF; R_0402_1005Metric
R103: 200R; R_0402_1005Metric
R201, R204: 5.1K; R_0402_1005Metric
R202, R203: 22R; R_0402_1005Metric
SW101: SW_SPST; SW_SPST_PTS810
SW102: 4P_button_sw; GT-TC026X-HXXX-LX
U102: W25Q128JVSIQ; SOP-8_5.28x5.23mm_P1.27mm
U103: RP2040; RP2040-QFN-56
U401: ME6211A33PG-N; SOT-89-3
Y101: 12Mhz; Crystal_SMD_3225-4Pin_3.2x2.5mm

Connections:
+1V1: C107.1, C117.1, C118.1, U103.23 (DVDD), U103.45 (VREG_VOUT), U103.50 (DVDD)
+VUSB: C201.2, C202.2, C401.1, L201.1, U401.2 (VIN); also elsewhere on the board
AMUX_OUT: U103.40 (GPIO28_ADC2); also elsewhere on the board
BUFDIR0: U103.2 (GPIO0); also elsewhere on the board
BUFDIR1: U103.3 (GPIO1); also elsewhere on the board
BUFDIR2: U103.4 (GPIO2); also elsewhere on the board
BUFDIR3: U103.5 (GPIO3); also elsewhere on the board
BUFDIR4: U103.6 (GPIO4); also elsewhere on the board
BUFDIR5: U103.7 (GPIO5); also elsewhere on the board
BUFDIR6: U103.8 (GPIO6); also elsewhere on the board
BUFDIR7: U103.9 (GPIO7); also elsewhere on the board
BUFIO0: U103.11 (GPIO8); also elsewhere on the board
BUFIO1: U103.12 (GPIO9); also elsewhere on the board
BUFIO2: U103.13 (GPIO10); also elsewhere on the board
BUFIO3: U103.14 (GPIO11); also elsewhere on the board
BUFIO4: U103.15 (GPIO12); also elsewhere on the board
BUFIO5: U103.16 (GPIO13); also elsewhere on the board
BUFIO6: U103.17 (GPIO14); also elsewhere on the board
BUFIO7: U103.18 (GPIO15); also elsewhere on the board
BUTTONS: SW102.1, U103.39 (GPIO27_ADC1)
CURRENT_ADJ_MCU: U103.36 (GPIO24); also elsewhere on the board
CURRENT_SENSE: U103.41 (GPIO29_ADC3); also elsewhere on the board
DISPLAY_CS: U103.35 (GPIO23); also elsewhere on the board
DISPLAY_DP: U103.34 (GPIO22); also elsewhere on the board
FLASH_CS: U103.38 (GPIO26_ADC0); also elsewhere on the board
GND: C103.2, C104.2, C105.2, C106.2, C107.2, C108.1, C109.2, C110.2, C111.2, C112.2, C113.2, C114.2, C115.2, C116.2, C117.2, C118.2, C201.1, C202.1, C401.2, C402.2, J201.1, J202.A1B12 (GND), J202.B1A12 (GND), J202.S1 (SHIELD), J202.S2 (SHIELD), J202.S3 (SHIELD), J202.S4 (SHIELD), R201.1, R204.1, SW101.2 (B), U102.4 (VSS), U103.19 (TESTEN), U103.57 (GND), U401.1 (GND), Y101.2, Y101.4; also elsewhere on the board
unnamed: C105.1, U103.20 (XIN), Y101.1
unnamed: C106.1, U103.21 (XOUT), Y101.3
unnamed: C109.1, R103.2, U103.43 (ADC_AVDD)
unnamed: J202.A4B9 (VBUS), J202.B4A9 (VBUS), L201.2
unnamed: J202.A5 (CC1), R201.2
unnamed: J202.B5 (CC2), R204.2
unnamed: R101.2, SW101.1 (A)
QSPI_SCLK: U102.6 (CLK), U103.52 (QSPI_SCLK)
QSPI_SD0: U102.5 (DI), U103.53 (QSPI_SD0)
QSPI_SD1: U102.2 (DO), U103.55 (QSPI_SD1)
QSPI_SD2: U102.3 (WP), U103.54 (QSPI_SD2)
QSPI_SD3: U102.7 (HOLD), U103.51 (QSPI_SD3)
QSPI_SS: R101.1, R102.2, U102.1 (CS), U103.56 (QSPI_SS)
RGB_CDO: U103.28 (GPIO17); also elsewhere on the board
SHIFT_EN: U103.32 (GPIO21); also elsewhere on the board
SHIFT_LATCH: U103.31 (GPIO20); also elsewhere on the board
SPI_CDI: U103.27 (GPIO16); also elsewhere on the board
SPI_CDO: U103.30 (GPIO19); also elsewhere on the board
SPI_CLK: U103.29 (GPIO18); also elsewhere on the board
SWCLK: J201.3, U103.24 (SWCLK)
SWDIO: J201.2, U103.25 (SWD)
USB_D+: R203.1, U103.47 (USB_DP)
USB_D-: R202.1, U103.46 (USB_DM)
USB_N: J202.A7 (DN1), J202.B7 (DN2), R202.2
USB_P: J202.A6 (DP1), J202.B6 (DP2), R203.2
VREG_ADJ_MCU: U103.37 (GPIO25); also elsewhere on the board

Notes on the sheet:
Power supply
0-2ohms ESR
USB connector
J202 is the bog standard, most common Chinese USB C connector.
Program flash
Programming header
Y101: 3225 package is cheapest, smallest, widely available crystal at the moment
Worst case power budget is 220mA during full buffer short. Sized for 145mA max, 100mA typical. C402 can be a ceremic capacitor with 0-2ohms ESR
